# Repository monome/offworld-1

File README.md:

# offworld-1
usb power splitter

oshpark quicklink: https://oshpark.com/shared_projects/obwYxr6T

bom, stocked at http://digikey.com

* 1 usb A, WM7087CT-ND
* 2 usb mini-B, WM17115-ND

.dxf file can be laser cut, 2 copies for top and bottom covers.

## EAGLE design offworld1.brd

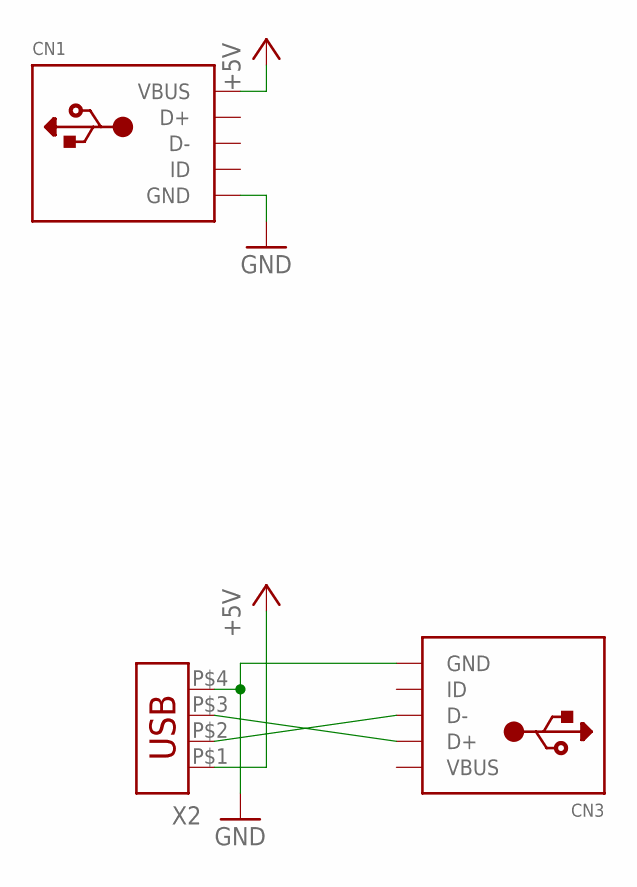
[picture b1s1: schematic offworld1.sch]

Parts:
CN1, CN3: USBMOLEX; USB-MINIB-THM-MOLEX
X2: USB-787616MID; USBA-MID

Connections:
+5V: CN1.VBUS, X2.P$1 (1)
GND: CN1.GND, CN3.GND, X2.P$4 (4)
unnamed: CN3.D+, X2.P$3 (3)
unnamed: CN3.D-, X2.P$2 (2)
VBUS: CN3.VBUS

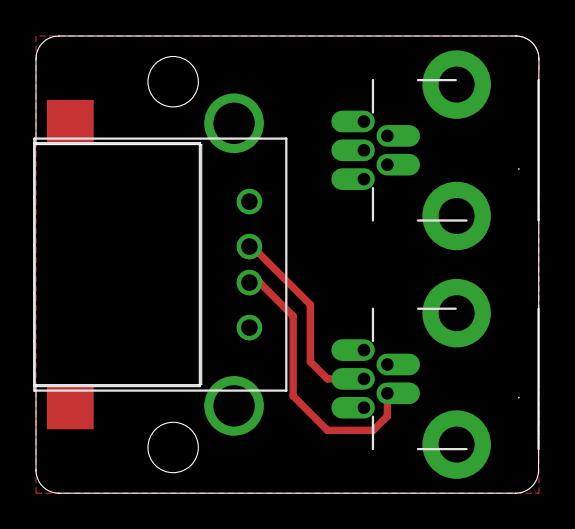
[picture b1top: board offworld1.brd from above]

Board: 2 copper layers, 27.9 x 25.4 mm, 3 parts (0 on the bottom side), 4 nets.

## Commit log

2017-10-02 initial
2017-10-02 readme
